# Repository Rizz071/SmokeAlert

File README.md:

# 🚨 SmokeAlert

**SmokeAlert** — это интеллектуальная беспроводная система пожарной сигнализации, разработанная для обеспечения безопасности в **жилых** и **промышленных** помещениях. Система сочетает в себе **долговечность**, **простоту установки** и **современные технологии связи**.

---

## 🔥 Основные особенности

- 📡 **LoRa 868MHz** — стабильная беспроводная связь с большим радиусом действия, не требующая государственной регистрации.
- 🛠️ **Установка за минуты** — настройка и добавление новых датчиков предельно упрощены.
- 📱 **Интеграция со смартфоном** — мгновенные уведомления и тревоги в приложении (через протокол MQTT, на собственной инфраструктуре).
- 🔋 **Долгий срок службы** — работа каждого датчика от 2 батареек AA до **1 года** без замены.
- ➕ **Гибкая масштабируемость** — к одной базовой станции можно подключить любое нужное количество датчиков.
- 🌐 **Два варианта выхода в интернет**:
  - через **Wi-Fi**
  - через **GSM-модуль**, где нет локальной сети

---

## ⚙️ Применение

- Частные дома и квартиры
- Офисы и административные здания
- Склады, мастерские, производственные помещения
- Объекты без постоянного подключения к WiFi

---

## 🤝 Контакты и вклад

Pull request'ы и предложения приветствуются!  
По вопросам сотрудничества — обращайтесь в [Issues](https://github.com/Rizz071/smokealert/issues) или откройте дискуссию.

---

**SmokeAlert** — безопасность должна быть доступной.

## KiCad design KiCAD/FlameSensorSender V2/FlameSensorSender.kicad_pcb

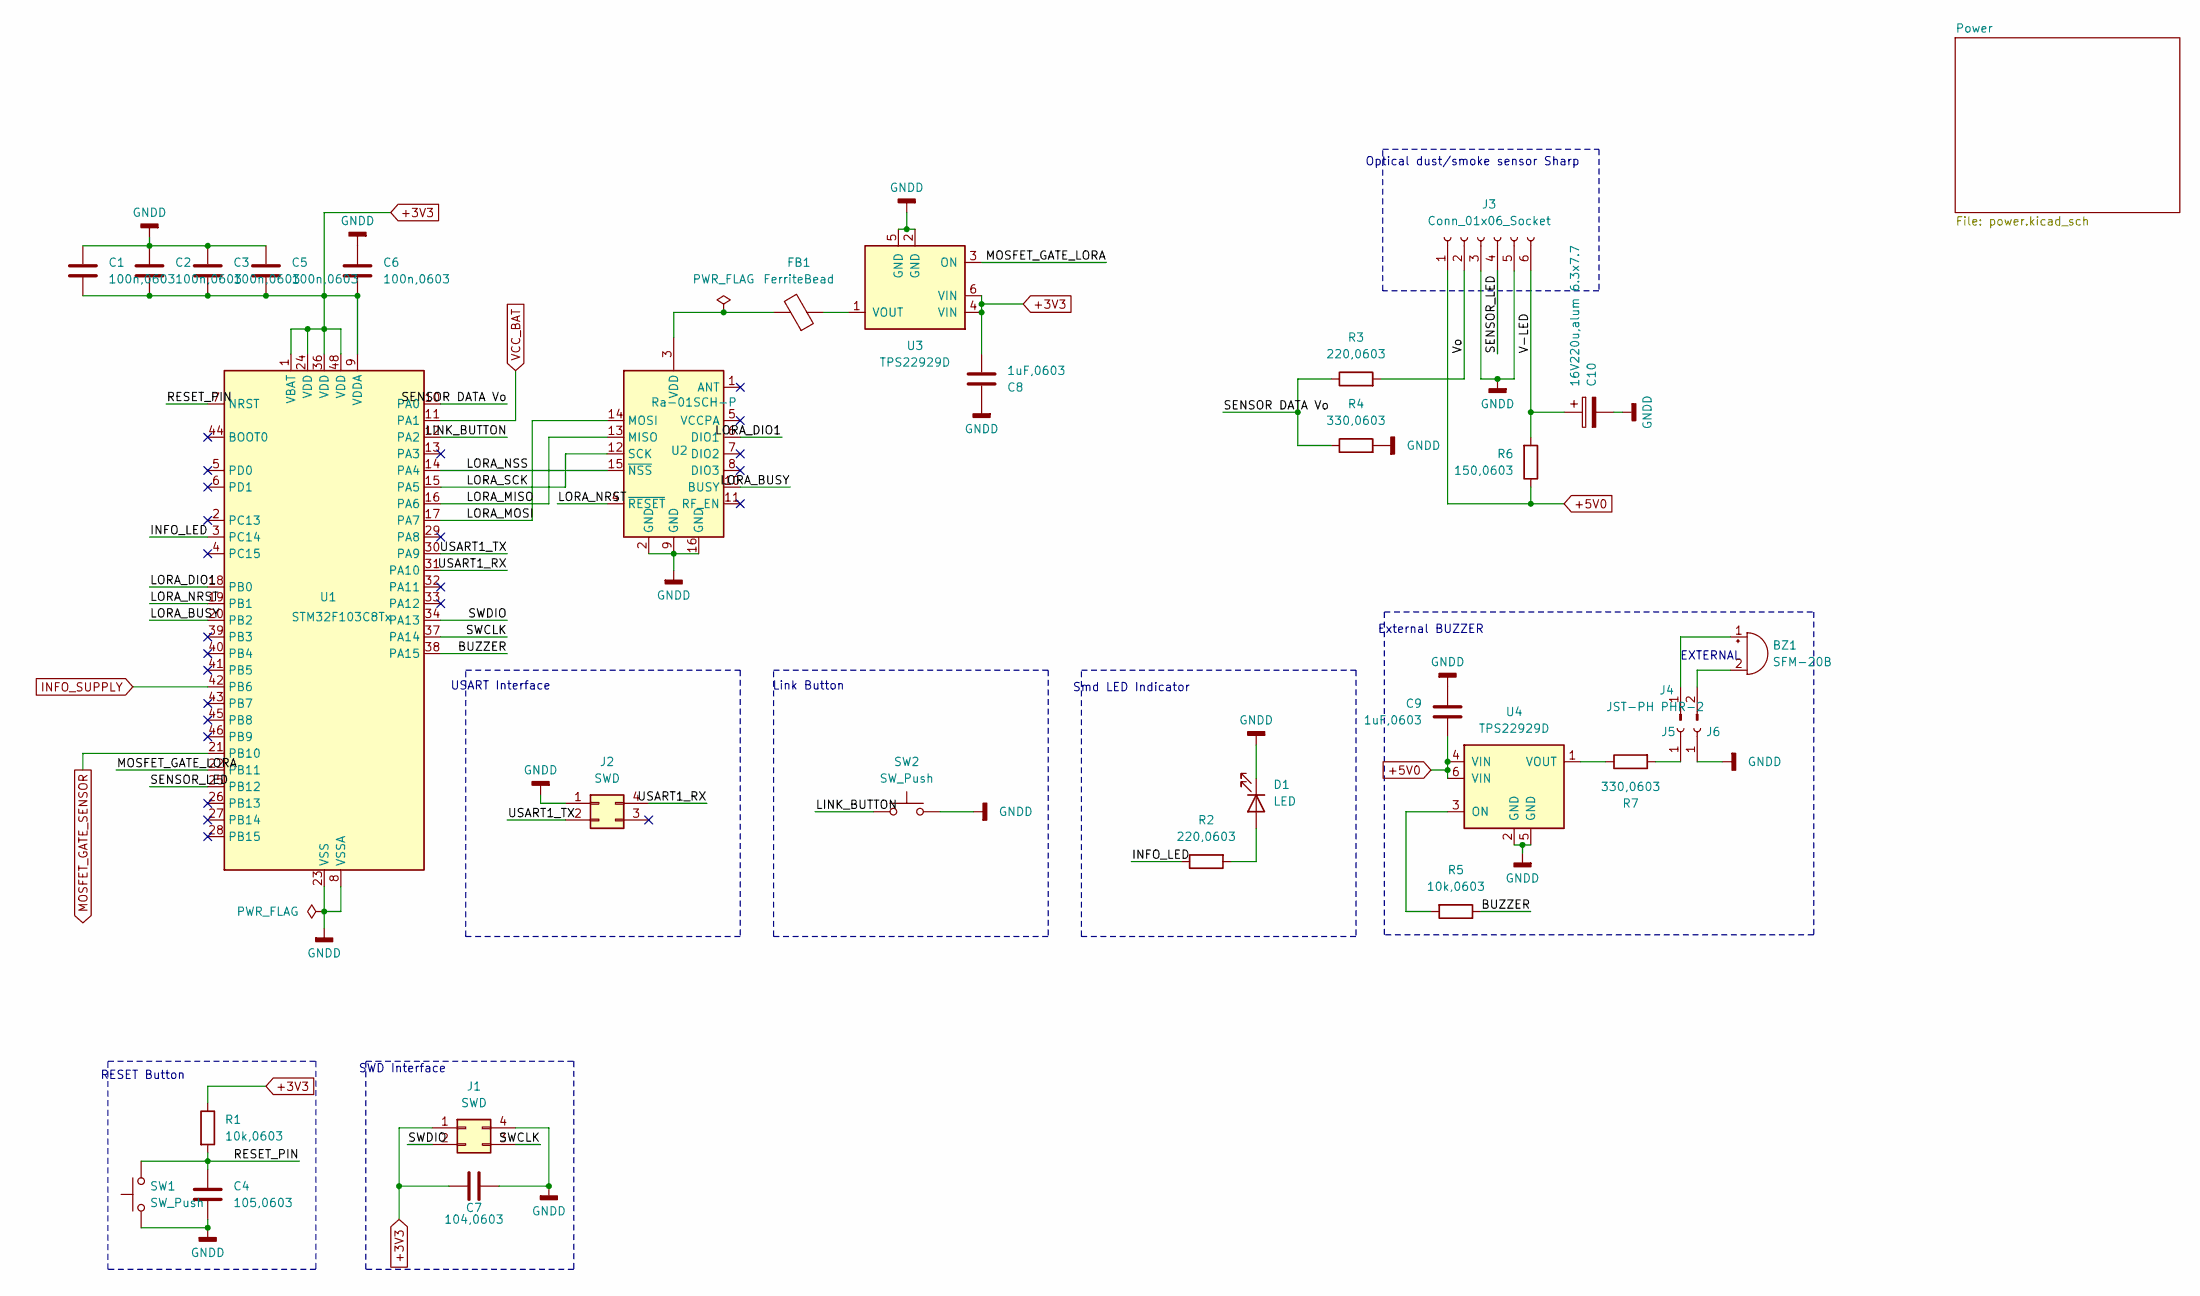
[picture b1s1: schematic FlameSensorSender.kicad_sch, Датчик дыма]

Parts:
BZ1: SFM-20B; Buzzer_12x9.5RM7.6
C1, C2, C3, C5, C6: 100n,0603; C_0603_1608Metric_Pad1.08x0.95mm_HandSolder
C4: 105,0603; C_0603_1608Metric_Pad1.08x0.95mm_HandSolder
C7: 104,0603; C_0603_1608Metric_Pad1.08x0.95mm_HandSolder
C8, C9: 1uF,0603; C_0603_1608Metric_Pad1.08x0.95mm_HandSolder
C10: 16V220u,alum 6.3x7.7; CP_Elec_6.3x7.7
D1: LED; LED_1206_3216Metric_Pad1.42x1.75mm_HandSolder
FB1: FerriteBead; L_0603_1608Metric_Pad1.05x0.95mm_HandSolder
J1, J2: SWD; PinHeader_2x02_P2.54mm_Vertical
J3: Conn_01x06_Socket; CONN_B6B-ZR-SM4-TF_JST
J4: JST-PH PHR-2
J5, J6: Conn_01x01_Socket; SolderWirePad_1x01_SMD_2x4mm
R1, R5: 10k,0603; R_0603_1608Metric_Pad0.98x0.95mm_HandSolder
R2, R3: 220,0603; R_0603_1608Metric_Pad0.98x0.95mm_HandSolder
R4, R7: 330,0603; R_0603_1608Metric_Pad0.98x0.95mm_HandSolder
R6: 150,0603; R_0603_1608Metric_Pad0.98x0.95mm_HandSolder
SW1: SW_Push; SW_PUSH_6mm_H4.3mm
SW2: SW_Push; SW_Push_1TS009xxxx-xxxx-xxxx_6x6x5mm
U1: STM32F103C8Tx; LQFP-48_7x7mm_P0.5mm
U2: Ra-01SCH-P; Ai-Thinker-Ra-01-LoRa
U3, U4: TPS22929D; SOT-23-6

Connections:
+3V3: C1.1, C2.1, C3.1, C5.1, C6.1, C7.2, C8.1, J1.1, R1.1, U1.1 (VBAT), U1.9 (VDDA), U1.24 (VDD), U1.36 (VDD), U1.48 (VDD), U3.4 (VIN), U3.6 (VIN); also elsewhere on the board
+5V0: C9.1, J3.1, R6.1, U4.4 (VIN), U4.6 (VIN); also elsewhere on the board
/BUZZER: R5.1, U1.38 (PA15)
/INFO_LED: R2.1, U1.3 (PC14)
/LINK_BUTTON: SW2.1, U1.12 (PA2)
/LORA_BUSY: U1.20 (PB2), U2.10 (BUSY)
/LORA_DIO1: U1.18 (PB0), U2.6 (DIO1)
/LORA_MISO: U1.16 (PA6), U2.13 (MISO)
/LORA_MOSI: U1.17 (PA7), U2.14 (MOSI)
/LORA_NRST: U1.19 (PB1), U2.4 (~RESET)
/LORA_NSS: U1.14 (PA4), U2.15 (~NSS)
/LORA_SCK: U1.15 (PA5), U2.12 (SCK)
/MOSFET_GATE_LORA: U1.22 (PB11), U3.3 (ON)
/RESET_PIN: C4.1, R1.2, SW1.2, U1.7 (NRST)
/SENSOR DATA Vo: R3.1, R4.1, U1.10 (PA0)
/SENSOR_LED: J3.4, U1.25 (PB12)
/SWCLK: J1.3, U1.37 (PA14)
/SWDIO: J1.2, U1.34 (PA13)
/USART1_RX: J2.4, U1.31 (PA10)
/USART1_TX: J2.2, U1.30 (PA9)
/V-LED: C10.1, J3.6, R6.2
/Vo: J3.2, R3.2
GNDD: C1.2, C2.2, C3.2, C4.2, C5.2, C6.2, C7.1, C8.2, C9.2, C10.2, D1.1 (K), J1.4, J2.1, J3.3, J3.5, J6.1, R4.2, SW1.1, SW2.2, U1.8 (VSSA), U1.23 (VSS), U1.35 (VSS), U1.47 (VSS), U2.2 (GND), U2.9 (GND), U2.16 (GND), U3.2 (GND), U3.5 (GND), U4.2 (GND), U4.5 (GND); also elsewhere on the board
INFO_SUPPLY: U1.42 (PB6); also elsewhere on the board
MOSFET_GATE_SENSOR: U1.21 (PB10); also elsewhere on the board
unnamed: BZ1.1 (+), J4.1
unnamed: BZ1.2 (-), J4.2
unnamed: D1.2 (A), R2.2
unnamed: J5.1, R7.2
unnamed: FB1.2, U2.3 (VDD)
unnamed: FB1.1, U3.1 (VOUT)
unnamed: R5.2, U4.3 (ON)
unnamed: R7.1, U4.1 (VOUT)
VCC_BAT: U1.11 (PA1); also elsewhere on the board

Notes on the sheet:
SWD Interface
RESET Button
Smd LED Indicator
Link Button
USART Interface
External BUZZER
Optical dust/smoke sensor Sharp
EXTERNAL

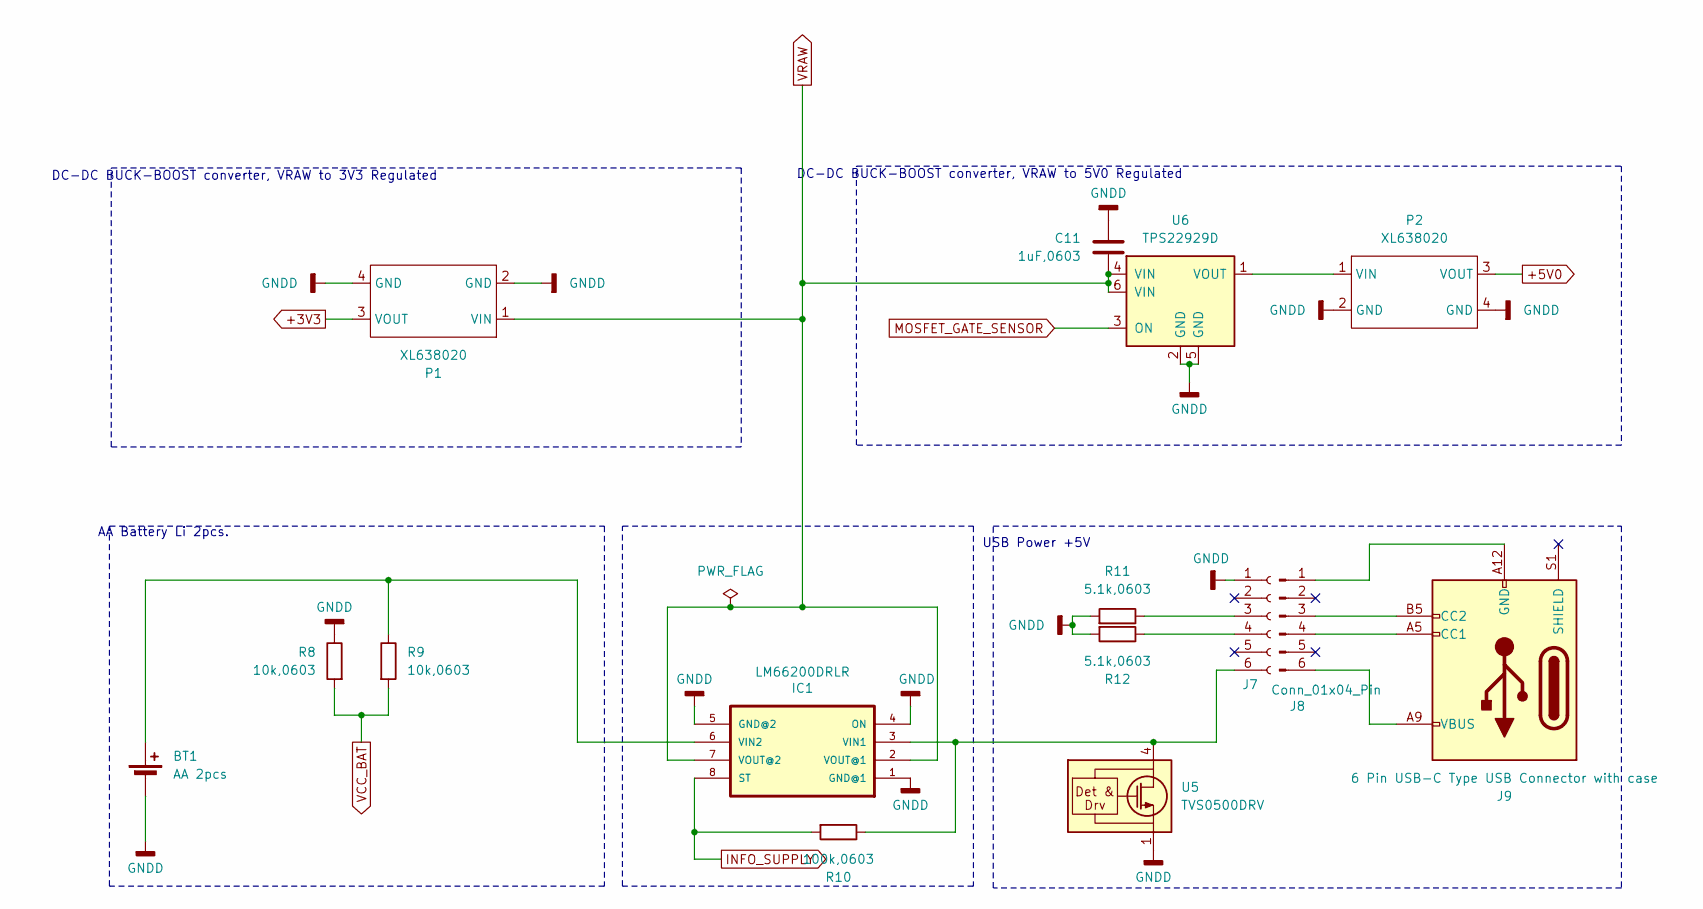
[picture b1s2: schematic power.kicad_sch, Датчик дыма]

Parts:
BT1: AA 2pcs; BatteryHolder_Keystone_2462_2xAA
C11: 1uF,0603; C_0603_1608Metric_Pad1.08x0.95mm_HandSolder
IC1: LM66200DRLR; SOT-5X3_DRL_TEX-M
J7: Conn_01x06_Socket; JST_PH_B6B-PH-K_1x06_P2.00mm_Vertical
J8: Conn_01x04_Pin
J9: 6 Pin USB-C Type USB Connector with case
P1, P2: XL638020; XL63802
R8, R9: 10k,0603; R_0603_1608Metric_Pad0.98x0.95mm_HandSolder
R10: 100k,0603; R_0603_1608Metric_Pad0.98x0.95mm_HandSolder
R11, R12: 5.1k,0603; R_0603_1608Metric_Pad0.98x0.95mm_HandSolder
U5: TVS0500DRV; WSON-6-1EP_2x2mm_P0.65mm_EP1x1.6mm
U6: TPS22929D; SOT-23-6

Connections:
+3V3: P1.3 (VOUT); also elsewhere on the board
+5V0: P2.3 (VOUT); also elsewhere on the board
GNDD: BT1.2 (-), C11.2, IC1.1 (GND@1), IC1.4 (ON), IC1.5 (GND@2), J7.1, P1.2 (GND), P1.4 (GND), P2.2 (GND), P2.4 (GND), R8.1, R11.2, R12.2, U5.1 (GND), U5.2 (GND), U5.3 (GND), U5.7 (GND), U6.2 (GND), U6.5 (GND); also elsewhere on the board
INFO_SUPPLY: IC1.8 (ST), R10.2; also elsewhere on the board
MOSFET_GATE_SENSOR: U6.3 (ON); also elsewhere on the board
unnamed: BT1.1 (+), IC1.6 (VIN2), R9.1
unnamed: IC1.3 (VIN1), J7.6, R10.1, U5.4 (IN), U5.5 (IN), U5.6 (IN)
unnamed: J7.3, R11.1
unnamed: J7.4, R12.1
unnamed: J8.1, J9.A12 (GND), J9.B12 (GND)
unnamed: J8.3, J9.B5 (CC2)
unnamed: J8.4, J9.A5 (CC1)
unnamed: J8.6, J9.A9 (VBUS), J9.B9 (VBUS)
unnamed: P2.1 (VIN), U6.1 (VOUT)
VCC_BAT: R8.2, R9.2; also elsewhere on the board
VRAW: C11.1, IC1.2 (VOUT@1), IC1.7 (VOUT@2), P1.1 (VIN), U6.4 (VIN), U6.6 (VIN)

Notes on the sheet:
AA Battery Li 2pcs.
DC-DC BUCK-BOOST converter, VRAW to 3V3 Regulated
DC-DC BUCK-BOOST converter, VRAW to 5V0 Regulated
USB Power +5V

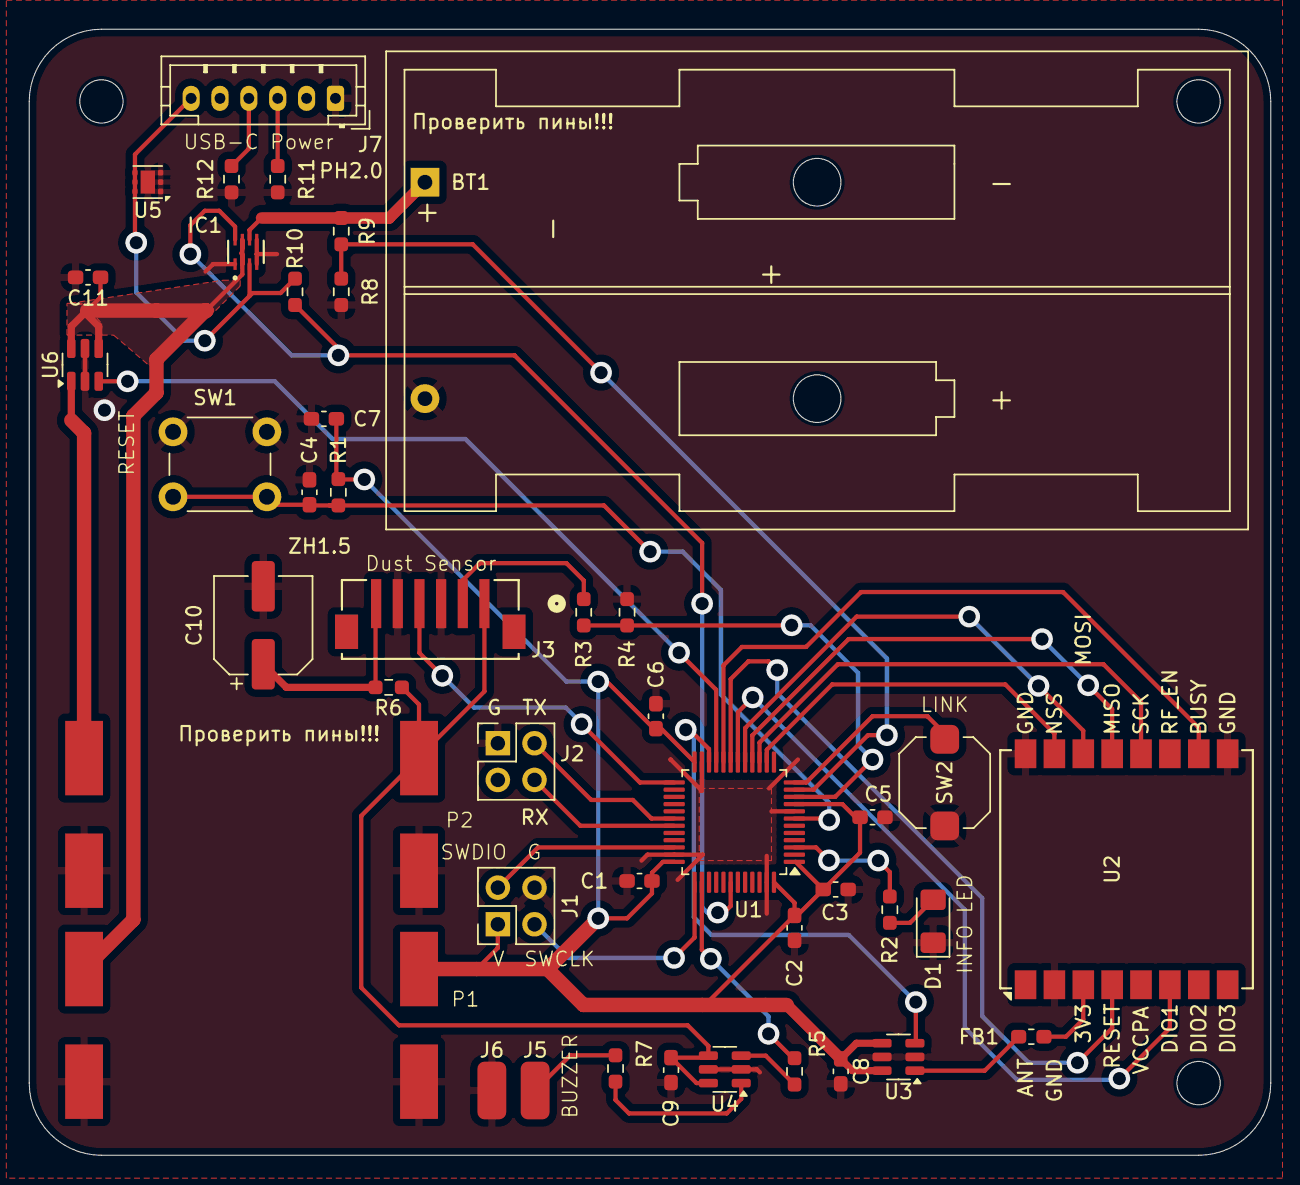
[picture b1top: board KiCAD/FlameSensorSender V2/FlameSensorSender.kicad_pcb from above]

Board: 2 copper layers, 86.0 x 78.0 mm, 43 parts (0 on the bottom side), 38 nets.

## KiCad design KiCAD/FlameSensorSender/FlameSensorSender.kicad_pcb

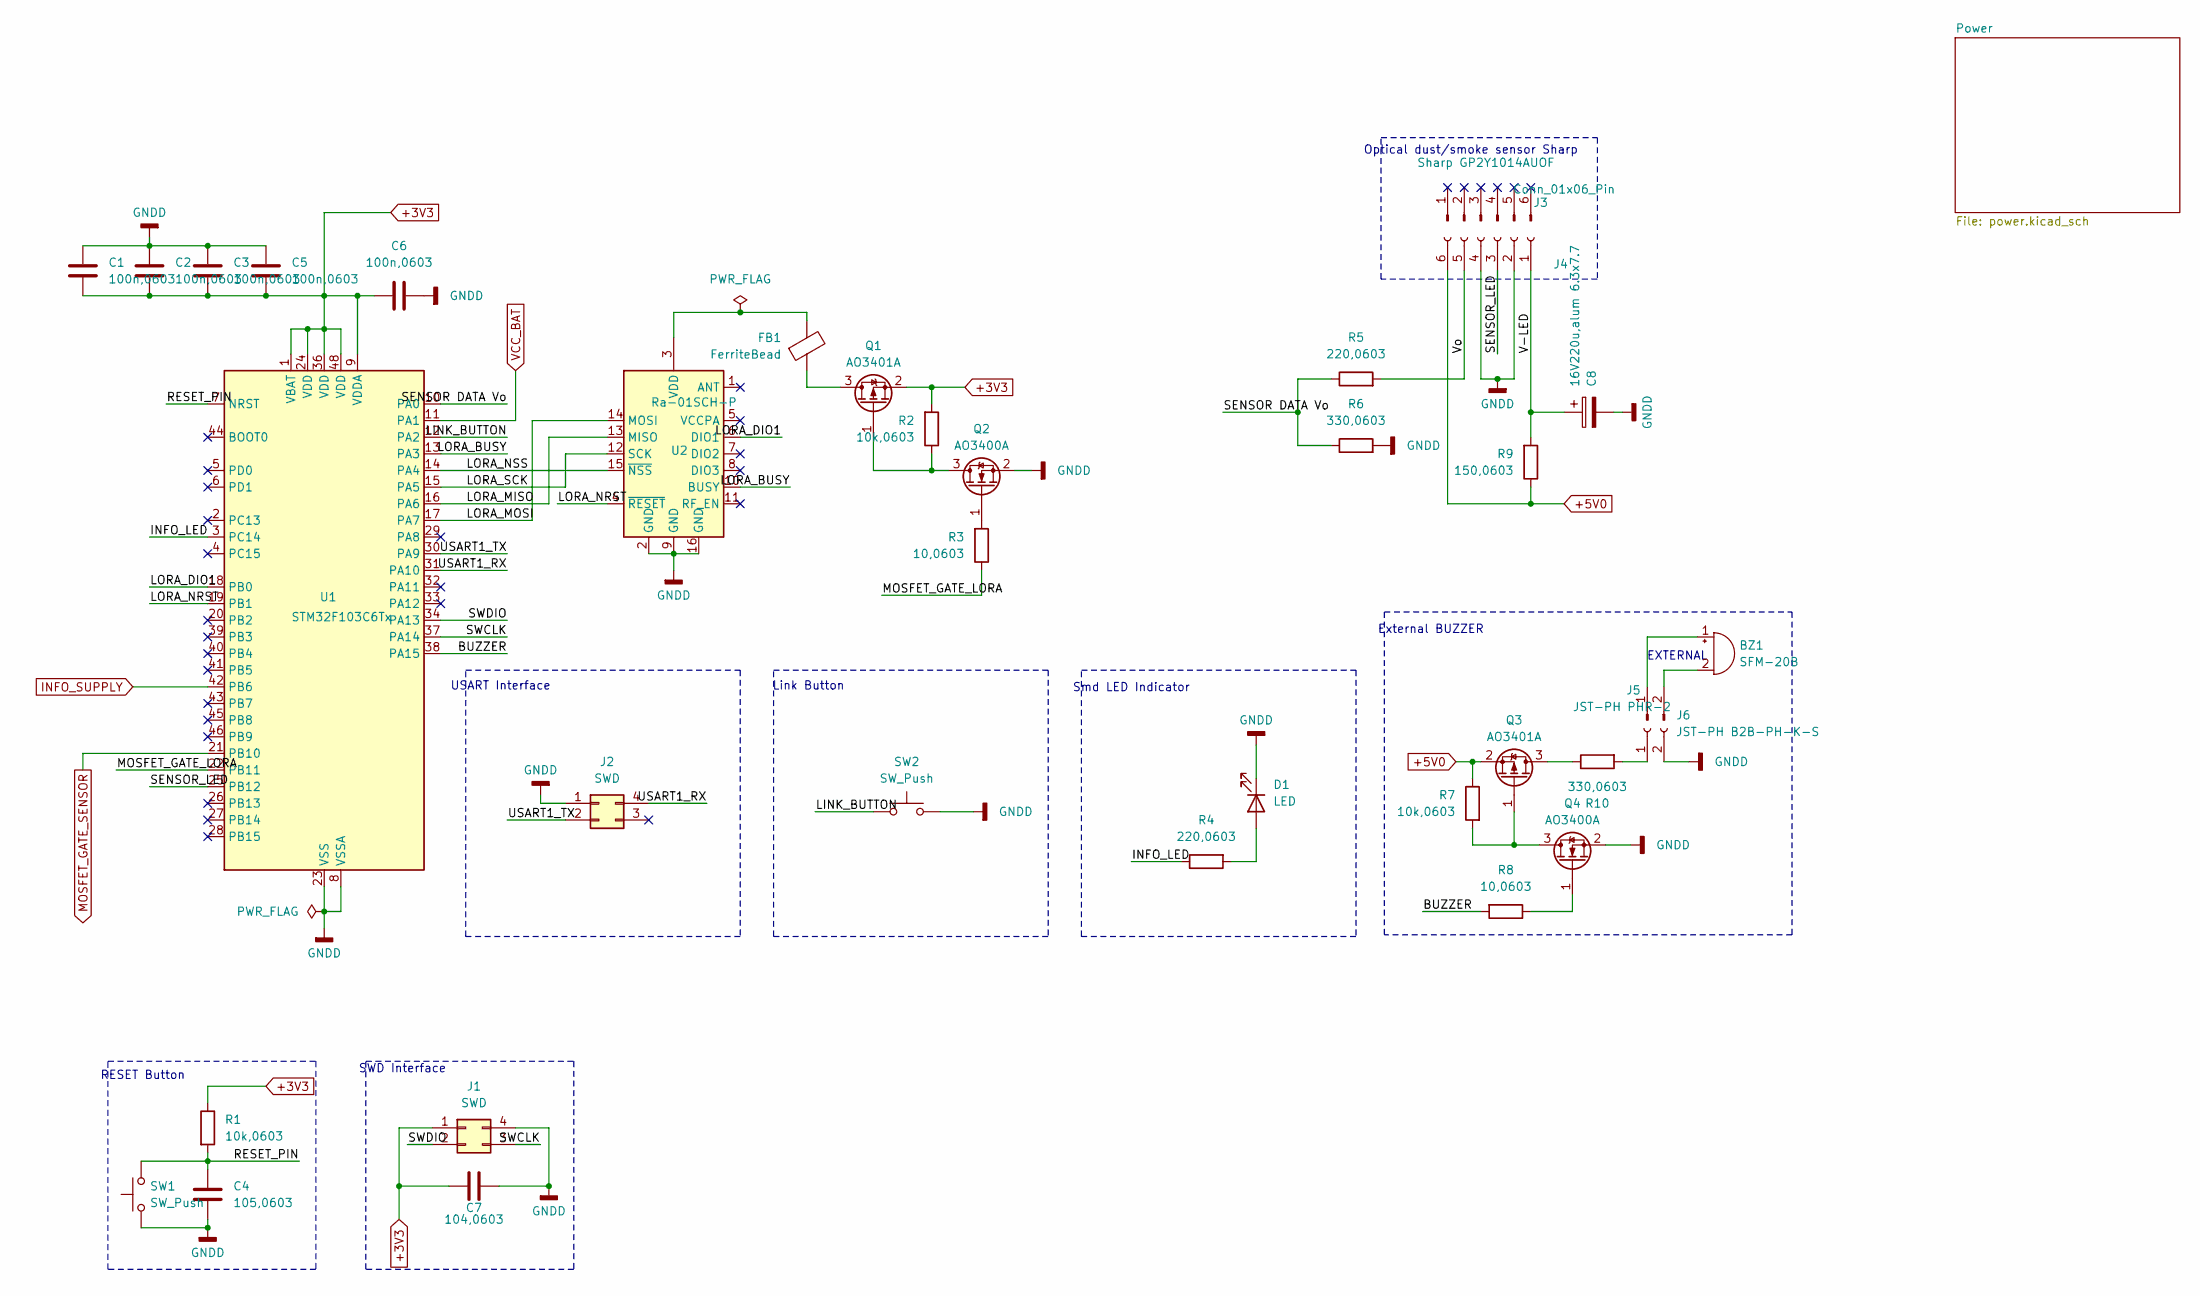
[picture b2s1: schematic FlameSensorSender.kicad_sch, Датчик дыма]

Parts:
BZ1: SFM-20B; Buzzer_12x9.5RM7.6
C1, C2, C3, C5, C6: 100n,0603; C_0603_1608Metric_Pad1.08x0.95mm_HandSolder
C4: 105,0603; C_0603_1608Metric_Pad1.08x0.95mm_HandSolder
C7: 104,0603; C_0603_1608Metric_Pad1.08x0.95mm_HandSolder
C8: 16V220u,alum 6.3x7.7; CP_Elec_6.3x7.7
D1: LED; LED_1206_3216Metric_Pad1.42x1.75mm_HandSolder
FB1: FerriteBead; L_0603_1608Metric_Pad1.05x0.95mm_HandSolder
J1, J2: SWD; PinHeader_2x02_P2.54mm_Vertical
J3: Conn_01x06_Pin; JST_PH_S6B-PH-K_1x06_P2.00mm_Horizontal
J4: Sharp GP2Y1014AUOF; JST_PH_S6B-PH-K_1x06_P2.00mm_Horizontal
J5: JST-PH PHR-2
J6: JST-PH B2B-PH-K-S; JST_PH_S2B-PH-K_1x02_P2.00mm_Horizontal
Q1, Q3: AO3401A; SOT-23-3
Q2, Q4: AO3400A; SOT-23-3
R1, R2, R7: 10k,0603; R_0603_1608Metric_Pad0.98x0.95mm_HandSolder
R3, R8: 10,0603; R_0603_1608Metric_Pad0.98x0.95mm_HandSolder
R4, R5: 220,0603; R_0603_1608Metric_Pad0.98x0.95mm_HandSolder
R6, R10: 330,0603; R_0603_1608Metric_Pad0.98x0.95mm_HandSolder
R9: 150,0603; R_0603_1608Metric_Pad0.98x0.95mm_HandSolder
SW1: SW_Push; SW_PUSH_6mm_H4.3mm
SW2: SW_Push; SW_Push_1TS009xxxx-xxxx-xxxx_6x6x5mm
U1: STM32F103C6Tx; LQFP-48_7x7mm_P0.5mm
U2: Ra-01SCH-P; Ai-Thinker-Ra-01-LoRa

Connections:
+3V3: C1.1, C2.1, C3.1, C5.1, C6.1, C7.2, J1.1, Q1.2 (S), R1.1, R2.2, U1.1 (VBAT), U1.9 (VDDA), U1.24 (VDD), U1.36 (VDD), U1.48 (VDD); also elsewhere on the board
+5V0: J4.6, Q3.2 (S), R7.1, R9.1; also elsewhere on the board
/BUZZER: R8.2, U1.38 (PA15)
/INFO_LED: R4.1, U1.3 (PC14)
/LINK_BUTTON: SW2.1, U1.12 (PA2)
/LORA_BUSY: U1.13 (PA3), U2.10 (BUSY)
/LORA_DIO1: U1.18 (PB0), U2.6 (DIO1)
/LORA_MISO: U1.16 (PA6), U2.13 (MISO)
/LORA_MOSI: U1.17 (PA7), U2.14 (MOSI)
/LORA_NRST: U1.19 (PB1), U2.4 (~RESET)
/LORA_NSS: U1.14 (PA4), U2.15 (~NSS)
/LORA_SCK: U1.15 (PA5), U2.12 (SCK)
/MOSFET_GATE_LORA: R3.1, U1.22 (PB11)
/RESET_PIN: C4.1, R1.2, SW1.2, U1.7 (NRST)
/SENSOR DATA Vo: R5.1, R6.1, U1.10 (PA0)
/SENSOR_LED: J4.3, U1.25 (PB12)
/SWCLK: J1.3, U1.37 (PA14)
/SWDIO: J1.2, U1.34 (PA13)
/USART1_RX: J2.4, U1.31 (PA10)
/USART1_TX: J2.2, U1.30 (PA9)
/V-LED: C8.1, J4.1, R9.2
/Vo: J4.5, R5.2
GNDD: C1.2, C2.2, C3.2, C4.2, C5.2, C6.2, C7.1, C8.2, D1.1 (K), J1.4, J2.1, J4.2, J4.4, J6.2, Q2.2 (S), Q4.2 (S), R6.2, SW1.1, SW2.2, U1.8 (VSSA), U1.23 (VSS), U1.35 (VSS), U1.47 (VSS), U2.2 (GND), U2.9 (GND), U2.16 (GND); also elsewhere on the board
INFO_SUPPLY: U1.42 (PB6); also elsewhere on the board
MOSFET_GATE_SENSOR: U1.21 (PB10); also elsewhere on the board
unnamed: BZ1.1 (+), J5.1
unnamed: BZ1.2 (-), J5.2
unnamed: D1.2 (A), R4.2
unnamed: J6.1, R10.2
unnamed: FB1.1, Q1.3 (D)
unnamed: Q1.1 (G), Q2.3 (D), R2.1
unnamed: Q2.1 (G), R3.2
unnamed: Q3.3 (D), R10.1
unnamed: Q3.1 (G), Q4.3 (D), R7.2
unnamed: Q4.1 (G), R8.1
unnamed: FB1.2, U2.3 (VDD)
VCC_BAT: U1.11 (PA1); also elsewhere on the board

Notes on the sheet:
SWD Interface
RESET Button
Smd LED Indicator
Link Button
USART Interface
External BUZZER
Optical dust/smoke sensor Sharp
EXTERNAL

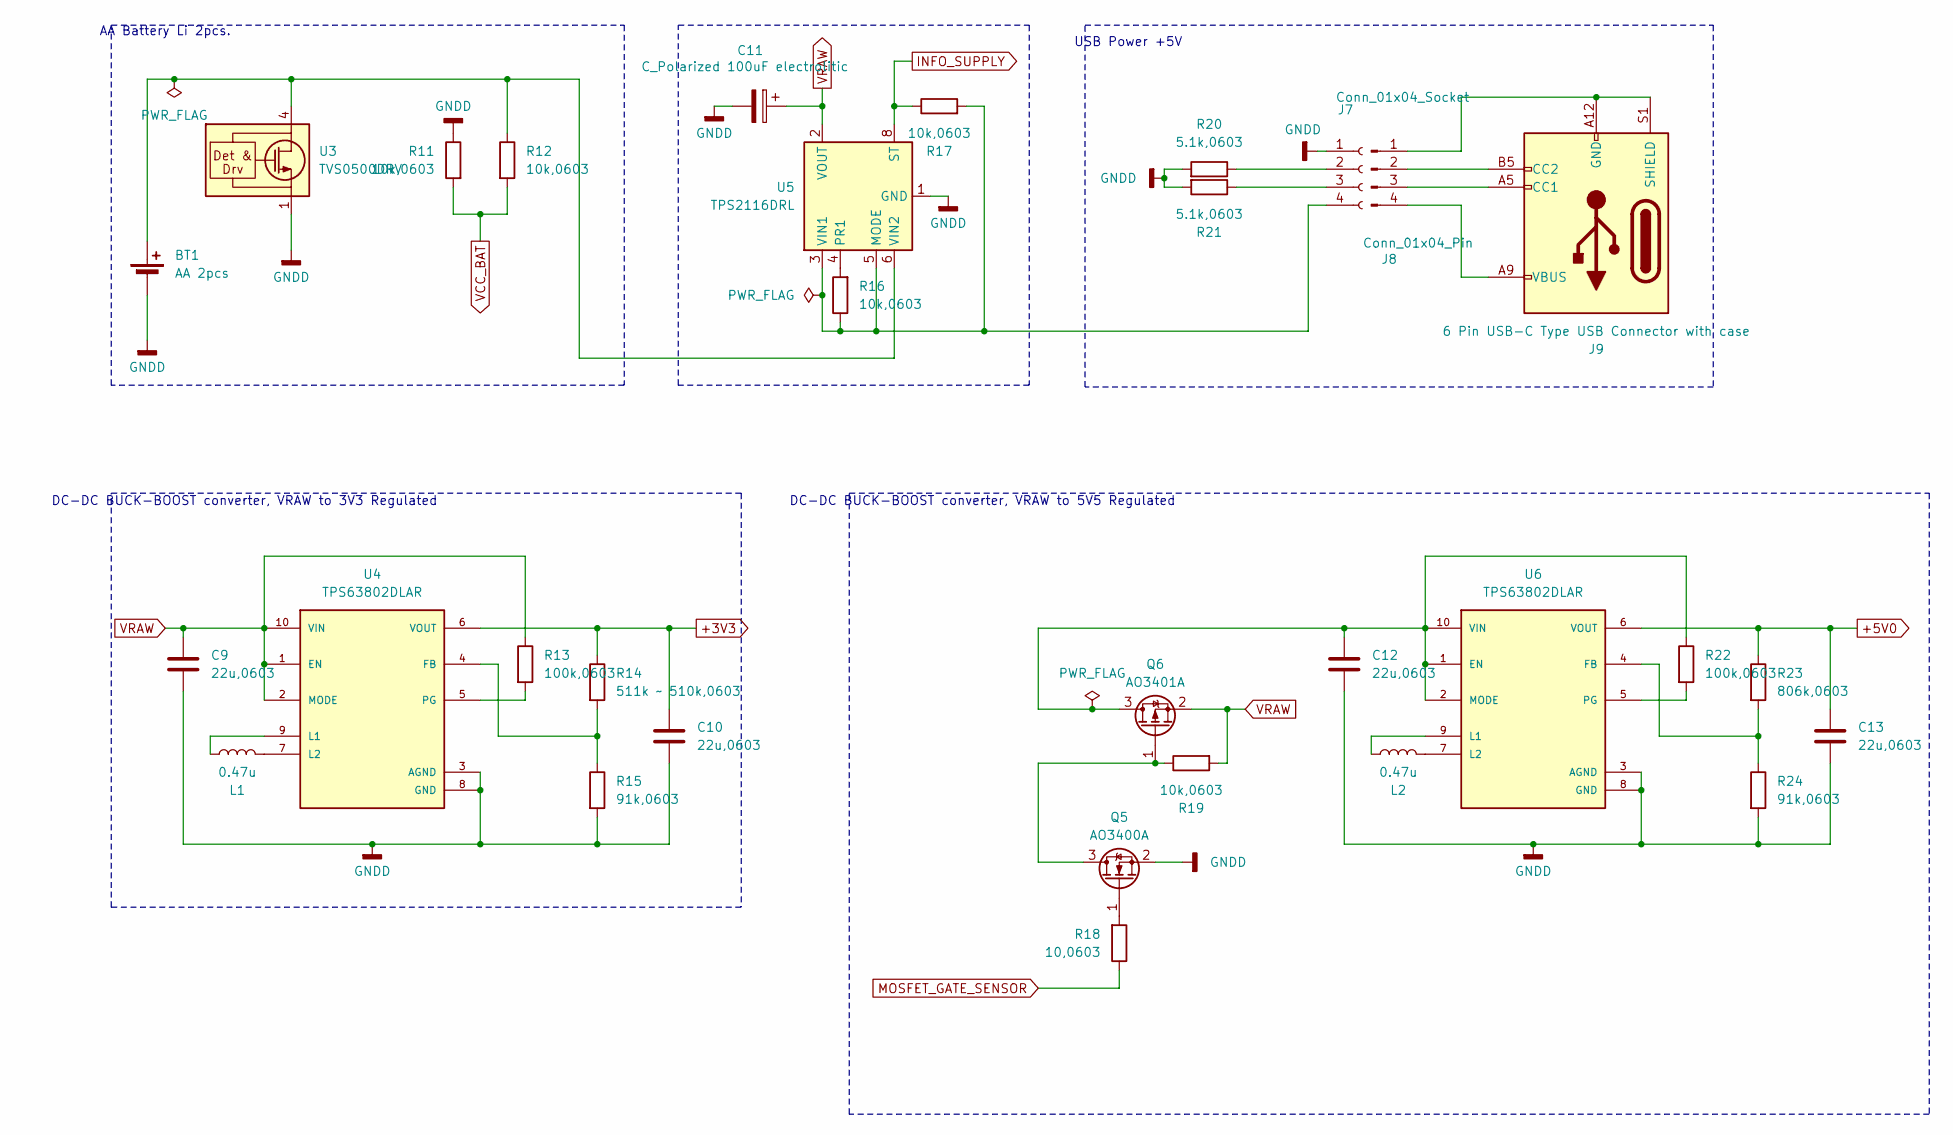
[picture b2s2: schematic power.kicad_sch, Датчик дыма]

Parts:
BT1: AA 2pcs; BatteryHolder_Keystone_2462_2xAA
C9, C10, C12, C13: 22u,0603; C_0603_1608Metric_Pad1.08x0.95mm_HandSolder
C11: C_Polarized 100uF electrolitic; CP_Elec_5x5.4
J7: Conn_01x04_Socket; JST_PH_S4B-PH-K_1x04_P2.00mm_Horizontal
J8: Conn_01x04_Pin
J9: 6 Pin USB-C Type USB Connector with case
L1, L2: 0.47u; INDC2016X120N
Q5: AO3400A; SOT-23-3
Q6: AO3401A; SOT-23-3
R11, R12, R16, R17, R19: 10k,0603; R_0603_1608Metric_Pad0.98x0.95mm_HandSolder
R13, R22: 100k,0603; R_0603_1608Metric_Pad0.98x0.95mm_HandSolder
R14: 511k ~ 510k,0603; R_0603_1608Metric_Pad0.98x0.95mm_HandSolder
R15, R24: 91k,0603; R_0603_1608Metric_Pad0.98x0.95mm_HandSolder
R18: 10,0603; R_0603_1608Metric_Pad0.98x0.95mm_HandSolder
R20, R21: 5.1k,0603; R_0603_1608Metric_Pad0.98x0.95mm_HandSolder
R23: 806k,0603; R_0603_1608Metric_Pad0.98x0.95mm_HandSolder
U3: TVS0500DRV; WSON-6-1EP_2x2mm_P0.65mm_EP1x1.6mm
U4, U6: TPS63802DLAR; VREG_TPS63802DLAR; PARTREV B
U5: TPS2116DRL; SOT-583-8

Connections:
+3V3: C10.1, R14.1, U4.6 (VOUT); also elsewhere on the board
+5V0: C13.1, R23.1, U6.6 (VOUT); also elsewhere on the board
GNDD: BT1.2 (-), C9.2, C10.2, C11.2, C12.2, C13.2, J7.1, Q5.2 (S), R11.1, R15.2, R20.2, R21.2, R24.2, U3.1 (GND), U3.2 (GND), U3.3 (GND), U3.7 (GND), U4.3 (AGND), U4.8 (GND), U5.1 (GND), U6.3 (AGND), U6.8 (GND); also elsewhere on the board
INFO_SUPPLY: R17.1, U5.8 (ST); also elsewhere on the board
MOSFET_GATE_SENSOR: R18.1; also elsewhere on the board
unnamed: BT1.1 (+), R12.1, U3.4 (IN), U3.5 (IN), U3.6 (IN), U5.6 (VIN2)
unnamed: J7.2, R20.1
unnamed: J7.3, R21.1
unnamed: J7.4, R16.1, R17.2, U5.3 (VIN1), U5.5 (MODE)
unnamed: J8.1, J9.A12 (GND), J9.B12 (GND), J9.S1 (SHIELD)
unnamed: J8.2, J9.B5 (CC2)
unnamed: J8.3, J9.A5 (CC1)
unnamed: J8.4, J9.A9 (VBUS), J9.B9 (VBUS)
unnamed: Q5.3 (D), Q6.1 (G), R19.1
unnamed: Q5.1 (G), R18.2
unnamed: C12.1, Q6.3 (D), R22.1, U6.1 (EN), U6.2 (MODE), U6.10 (VIN)
unnamed: R14.2, R15.1, U4.4 (FB)
unnamed: L1.2, U4.9 (L1)
unnamed: L1.1, U4.7 (L2)
unnamed: R13.2, U4.5 (PG)
unnamed: R16.2, U5.4 (PR1)
unnamed: R23.2, R24.1, U6.4 (FB)
unnamed: L2.2, U6.9 (L1)
unnamed: L2.1, U6.7 (L2)
unnamed: R22.2, U6.5 (PG)
VCC_BAT: R11.2, R12.2; also elsewhere on the board
VRAW: C9.1, C11.1, Q6.2 (S), R13.1, R19.2, U4.1 (EN), U4.2 (MODE), U4.10 (VIN), U5.2 (VOUT), U5.7 (VOUT)

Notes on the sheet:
AA Battery Li 2pcs.
DC-DC BUCK-BOOST converter, VRAW to 3V3 Regulated
DC-DC BUCK-BOOST converter, VRAW to 5V5 Regulated
USB Power +5V

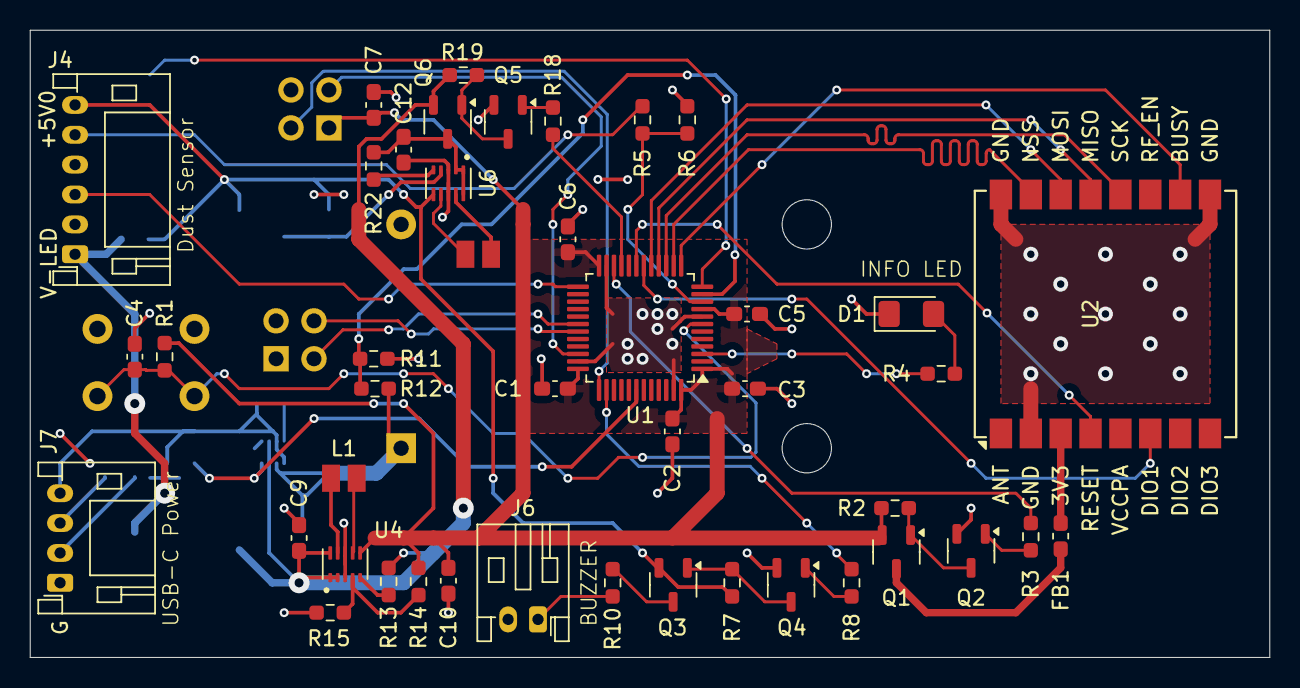
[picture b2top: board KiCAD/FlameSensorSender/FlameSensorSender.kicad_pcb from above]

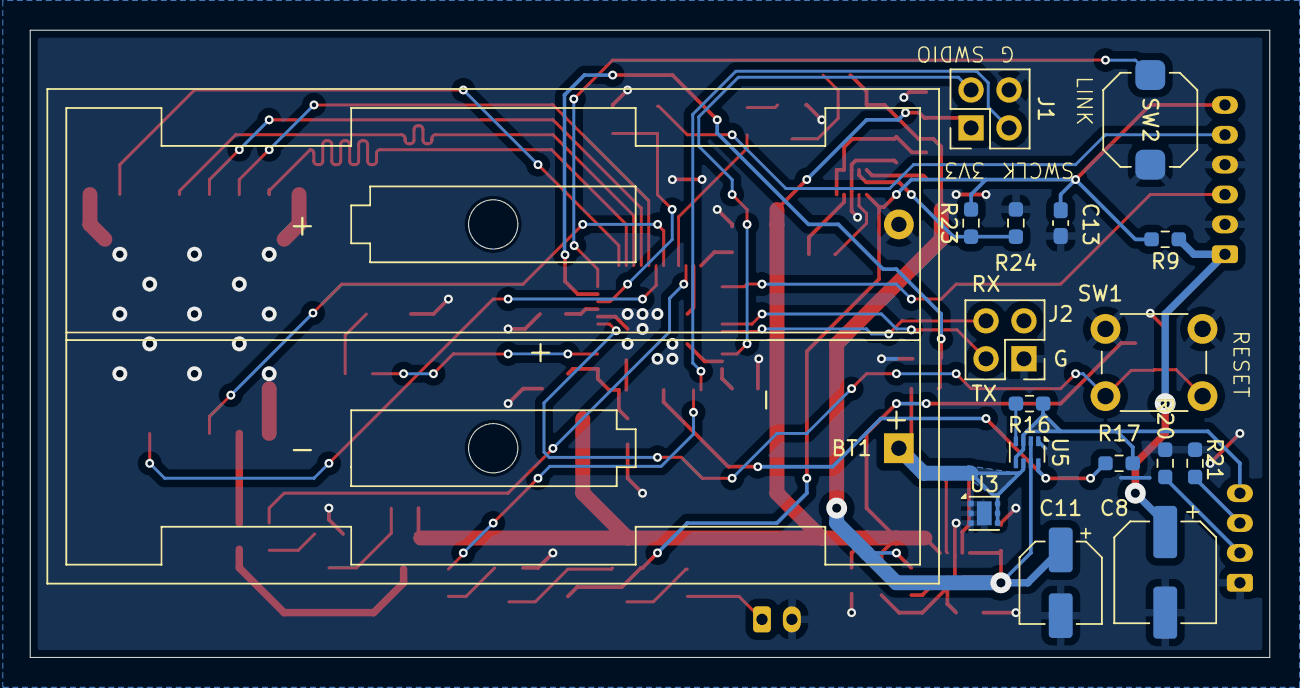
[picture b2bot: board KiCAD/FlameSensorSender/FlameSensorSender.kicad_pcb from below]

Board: 2 copper layers, 83.0 x 42.0 mm, 61 parts (17 on the bottom side), 52 nets.
